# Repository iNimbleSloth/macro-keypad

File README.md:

# macro-keypad
A small USB macro keypad designed to use Cherry MX or pin compatible switches.

Here’s an accompanying video showing the macro keypad in more detail.

See the use, design and coding on [YouTube](https://www.youtube.com/watch?v=2TVdBebZfKo)

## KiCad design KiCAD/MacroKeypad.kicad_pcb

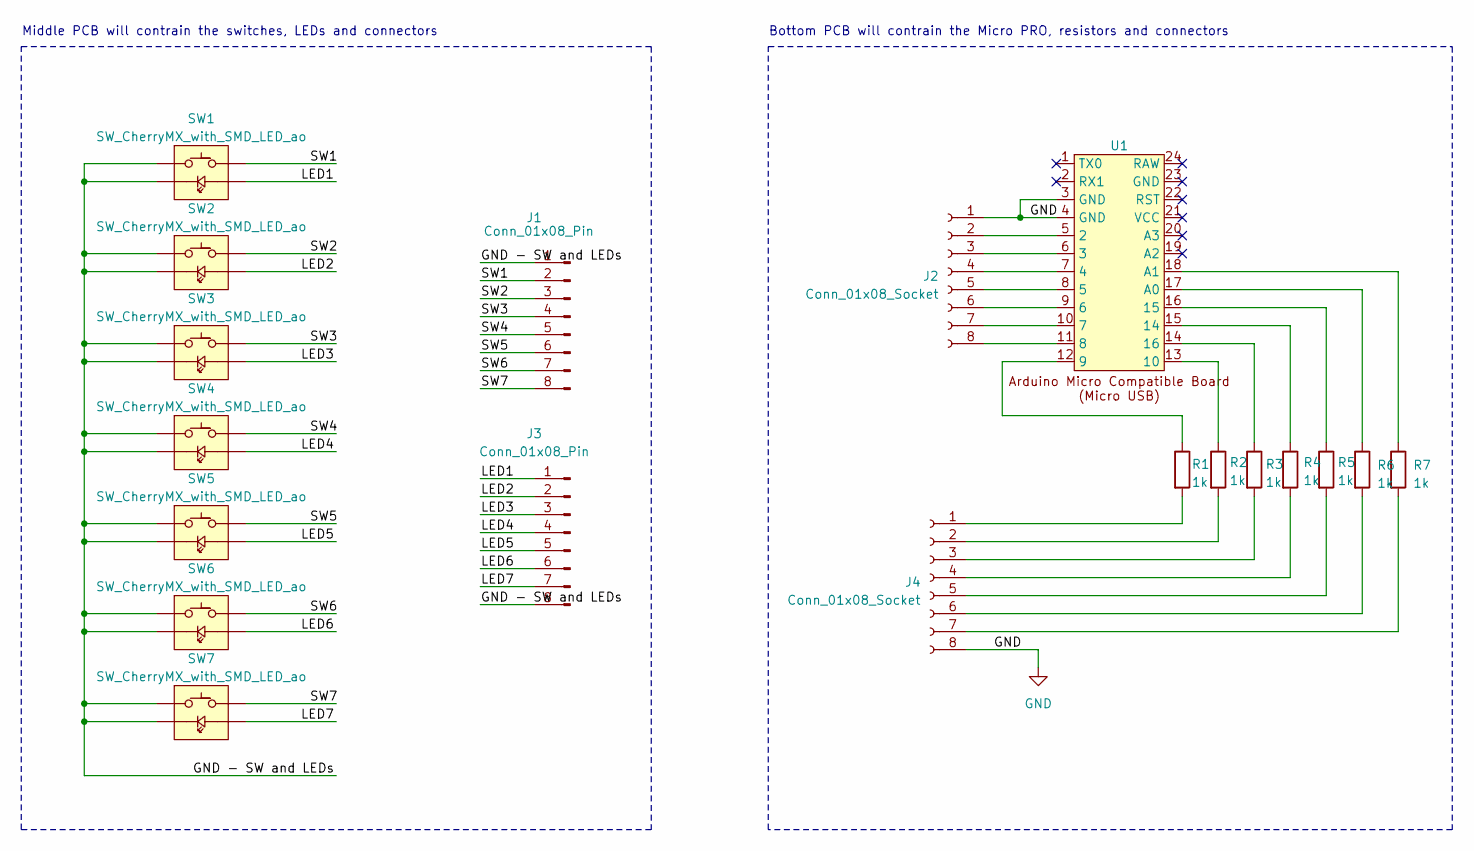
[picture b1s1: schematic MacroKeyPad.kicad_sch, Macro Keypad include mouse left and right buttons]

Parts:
J1, J3: Conn_01x08_Pin; PinHeader_1x08_P2.54mm_Vertical
J2, J4: Conn_01x08_Socket; PinSocket_1x08_P2.54mm_Vertical
R1, R2, R3, R4, R5, R6, R7: 1k; R_Axial_DIN0207_L6.3mm_D2.5mm_P10.16mm_Horizontal
SW1, SW2, SW3, SW4, SW5, SW6, SW7: SW_CherryMX_with_SMD_LED_ao; SW_Cherry_MX_1.00u_PCB_with SMD LED.kicad_AO
U1: ArduinoMicroCompatibleBoard

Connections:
/GND - SW and LEDs: J1.1, J3.8, SW1.1, SW1.3 (K), SW2.1, SW2.3 (K), SW3.1, SW3.3 (K), SW4.1, SW4.3 (K), SW5.1, SW5.3 (K), SW6.1, SW6.3 (K), SW7.1, SW7.3 (K)
/LED1: J3.1, SW1.4 (A)
/LED2: J3.2, SW2.4 (A)
/LED3: J3.3, SW3.4 (A)
/LED4: J3.4, SW4.4 (A)
/LED5: J3.5, SW5.4 (A)
/LED6: J3.6, SW6.4 (A)
/LED7: J3.7, SW7.4 (A)
/SW1: J1.2, SW1.2
/SW2: J1.3, SW2.2
/SW3: J1.4, SW3.2
/SW4: J1.5, SW4.2
/SW5: J1.6, SW5.2
/SW6: J1.7, SW6.2
/SW7: J1.8, SW7.2
GND: J2.1, J4.8, U1.3 (GND), U1.4 (GND)
unnamed: J2.2, U1.5 (2)
unnamed: J2.3, U1.6 (3)
unnamed: J2.4, U1.7 (4)
unnamed: J2.5, U1.8 (5)
unnamed: J2.6, U1.9 (6)
unnamed: J2.7, U1.10 (7)
unnamed: J2.8, U1.11 (8)
unnamed: J4.1, R1.2
unnamed: J4.2, R2.2
unnamed: J4.3, R3.2
unnamed: J4.4, R4.2
unnamed: J4.5, R5.2
unnamed: J4.6, R6.2
unnamed: J4.7, R7.2
unnamed: R1.1, U1.12 (9)
unnamed: R2.1, U1.13 (10)
unnamed: R4.1, U1.15 (14)
unnamed: R5.1, U1.16 (15)
unnamed: R3.1, U1.14 (16)
unnamed: R6.1, U1.17 (A0)
unnamed: R7.1, U1.18 (A1)

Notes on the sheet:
Bottom PCB will contrain the Micro PRO, resistors and connectors
Middle PCB will contrain the switches, LEDs and connectors

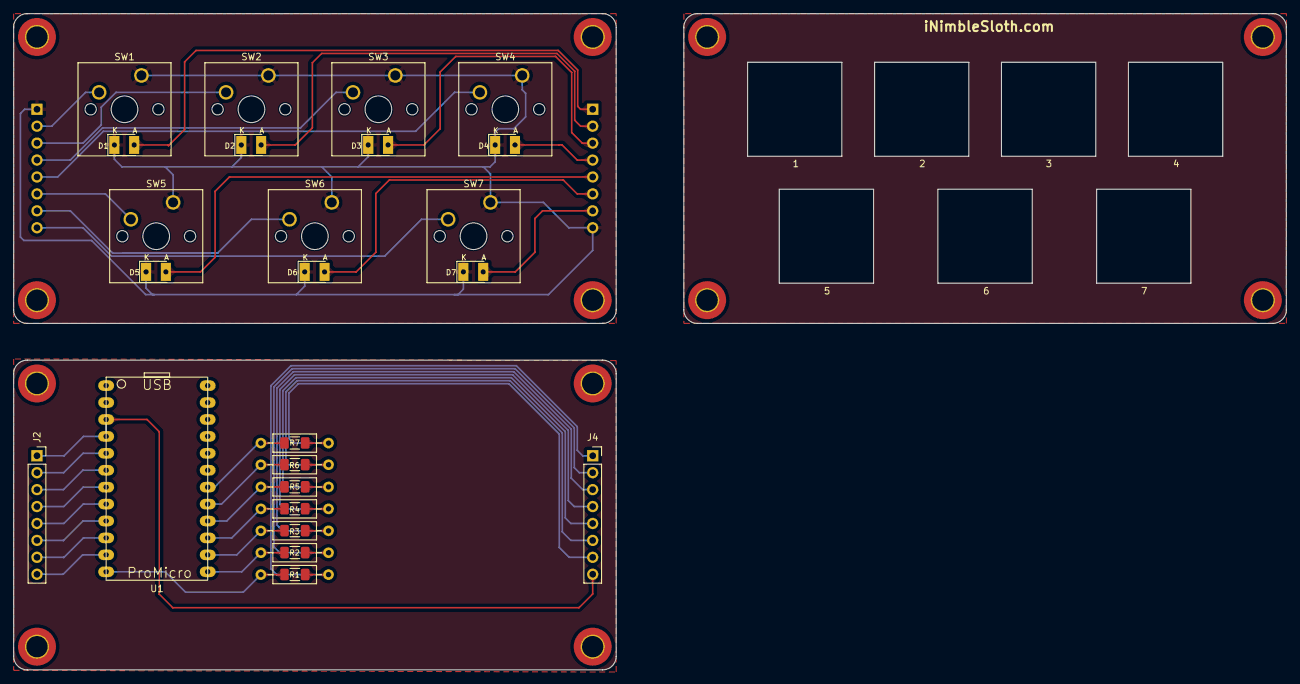
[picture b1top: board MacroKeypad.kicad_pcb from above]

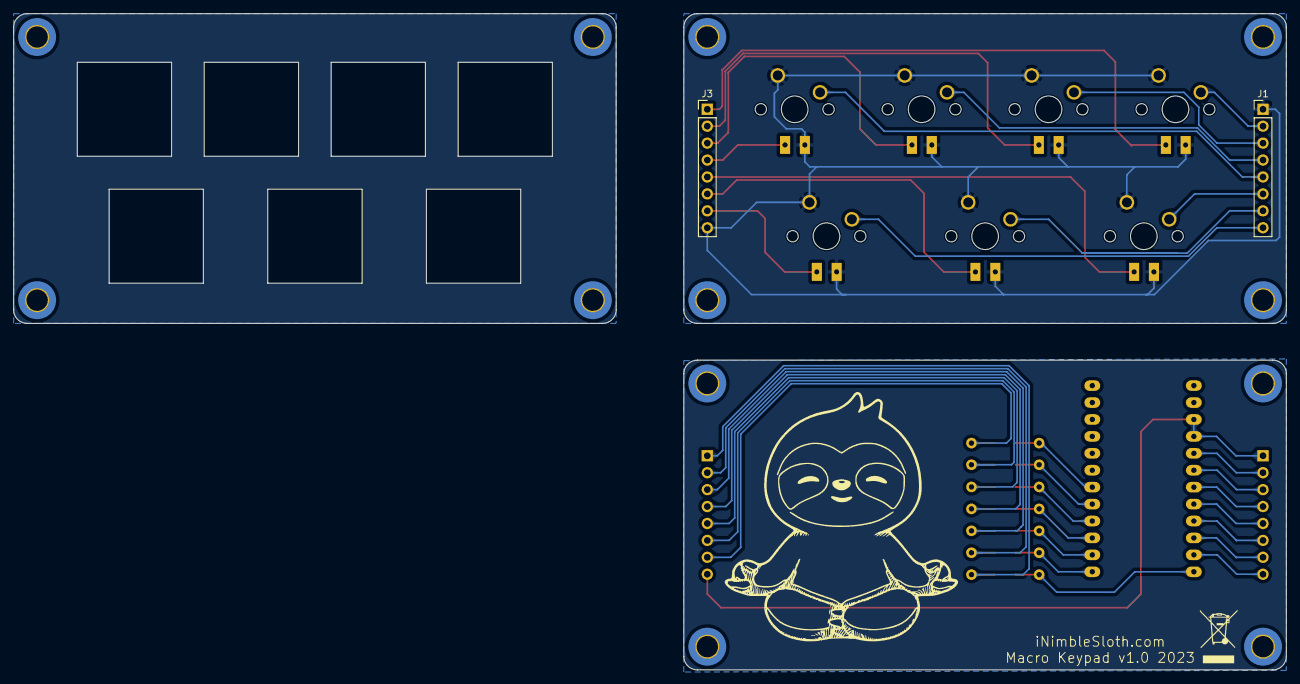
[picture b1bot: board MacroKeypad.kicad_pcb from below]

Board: 2 copper layers, 191.0 x 98.5 mm, 19 parts (2 on the bottom side), 37 nets.

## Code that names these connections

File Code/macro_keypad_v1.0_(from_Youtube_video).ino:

 /*  Macro Keypad
  by iNimbleSloth.com
  April 2023
*/
#include <Keyboard.h>
#include <Mouse.h>

//Create names for I/O; SW for input switches & led for LEDs in the switches.
//The Number is the Arduino pin out NOT the PCB pinout!!
int sw1 = 2;
int sw2 = 3;
int sw3 = 4;
int sw4 = 5;
int sw5 = 6;
int sw6 = 7;
int sw7 = 8;
int led1 = 9;
int led2 = 10;
int led3 = 16;
int led4 = 14;
int led5 = 15;
int led6 = 18;
int led7 = 19;

// variables to keep strack of button states
bool copyState = false;       // set initial state of Copy to false, i.e copy key not held down
bool pasteState = false;      // set initial state of paste to false, i.e copy key not held down
bool sw1State = false;        // set initial sate of sw1 to false
bool sw2State = false;        // set initial sate of sw2 to false
bool sw3State = false;        // set initial sate of sw3 to false
bool sw4State = false;        // set initial sate of sw4 to false
//bool sw5State = false;        // set initial sate of sw5 to false
//bool sw6State = false;        // set initial sate of sw6 to false
bool sw7State = false;        // set initial sate of sw7 to false

void setup() {

  Serial.begin(9600);           //serial output used for debugging (not required for release version)

  //setup I/O; SW inputs with internal pull up resistor. LEDs as outputs.
  pinMode(sw1, INPUT_PULLUP);
  pinMode(sw2, INPUT_PULLUP);
  pinMode(sw3, INPUT_PULLUP);
  pinMode(sw4, INPUT_PULLUP);
  pinMode(sw5, INPUT_PULLUP);
  pinMode(sw6, INPUT_PULLUP);
  pinMode(sw7, INPUT_PULLUP);
  pinMode(led1, OUTPUT);
  pinMode(led2, OUTPUT);
  pinMode(led3, OUTPUT);
  pinMode(led4, OUTPUT);
  pinMode(led5, OUTPUT);
  pinMode(led6, OUTPUT);
  pinMode(led7, OUTPUT);
}

//Main program loop starts here.
void loop() {
  //Serial.println("Start of Loop ");

  //SW1
  // IF SW1 is pressed AND the sw1State status is false (i.e. not already pressed), then type text
  if (digitalRead(sw1) == LOW && sw1State == false)
  {
    digitalWrite(led1, HIGH);
    sw1State = true;
    Keyboard.println("Case ");
    Keyboard.println("Create cLibrary acount and add username to contact in Salesforce.");
    Keyboard.println("Send through new technical contact lead.");
    delay(50);
  }
    
  // IF SW1 is released AND the sw3State status is true (i.e. button just released), then turn off the LED on the  button (SW1/LED1)
  if (digitalRead(sw1) == HIGH && sw1State == true)
  {
    digitalWrite(led1, LOW);
    sw1State = false;
    delay(50);
  }
    
  //SW2
  // IF SW2 is pressed AND the sw4State status is false (i.e. not already pressed), then type text
  if (digitalRead(sw2) == LOW && sw2State == false)
  {
    digitalWrite(led2, HIGH);
    sw2State = true;
    Keyboard.println("Created cLibrary acount and added username to contact in Salesforce.");
    Keyboard.println("Sent through new technical contact lead.");
    delay(50);
  }
    
  // IF SW4 is released AND the sw2State status is true (i.e. button just released), then turn off the LED on the snip button (SW2/LED2)
  if (digitalRead(sw2) == HIGH && sw2State == true)
  {
    digitalWrite(led2, LOW);
    sw2State = false;
    delay(50);
  }

  //SW3
  // IF SW3 is pressed and the sw5State status is false (i.e. not already pressed), then press type text
  if (digitalRead(sw3) == LOW && sw3State == false)
  {
    digitalWrite(led3, HIGH);
    sw3State = true;
    Keyboard.println("Case ");
    Keyboard.println("Create academy account.");
    Keyboard.println("Send lead through to quote for training.");
    delay(50);
  }
    
  // IF SW3 is released AND the snipeState status is true (i.e. button just released), then turn off the LED on the snip button (SW5/LED5)
  if (digitalRead(sw3) == HIGH && sw3State == true)
  {
    digitalWrite(led3, LOW);
    sw3State = false;
    delay(50);
  }

  //SW4 
  // IF SW4 is pressed and the sw4State status is false (i.e. not already pressed), then press type text
  if (digitalRead(sw4) == LOW && sw4State == false)
  {
    digitalWrite(led4, HIGH);
    sw4State = true;
    Keyboard.println("Created academy account.");
    Keyboard.println("Sent lead through to quote for training.");
    delay(50);
  }
    
  // IF SW4 is released AND the snipeState status is true (i.e. button just released), then turn off the LED on the snip button (SW4/LED4)
  if (digitalRead(sw4) == HIGH && sw4State == true)
  {
    digitalWrite(led4, LOW);
    sw4State = false;
    delay(50);
  }
    
  //SW5
  // IF SW5 is pressed and the copyState status is false (i.e. not already pressed), then execute Windows COPY command
  if (digitalRead(sw5) == LOW && copyState == false)
  {
    digitalWrite(led5, HIGH);
    copyState = true;
    Serial.println("Windows COPY command START");
    Keyboard.press(KEY_LEFT_CTRL);
    Keyboard.write('c');
    Keyboard.release(KEY_LEFT_CTRL);
    delay(50);
  }
    
  // IF SW5 is released AND the copyState status is true (i.e. button just released), then turn off the LED on the COPY button (SW5/LED5)
  if (digitalRead(sw5) == HIGH && copyState == true)
  {
    digitalWrite(led5, LOW);
    copyState = false;
    Serial.println("Windows COPY command END");
    delay(50);
  }

  //SW6 
  // IF SW6 is pressed AND the pasteState status is false (i.e. not already pressed), then execute Windows PASTE command
  if (digitalRead(sw6) == LOW && pasteState == false)
  {
    digitalWrite(led6, HIGH);
    pasteState = true;
    Serial.println("Windows PASTE command START");
    Keyboard.press(KEY_LEFT_CTRL);
    Keyboard.write('v');
    Keyboard.release(KEY_LEFT_CTRL);
    delay(50);
  }
    
  // IF SW6 is released AND the pasteState status is true (i.e. button just released), then turn off the LED on the PASTE button (SW3/LED3)
  if (digitalRead(sw6) == HIGH && pasteState == true)
  {
    digitalWrite(led6, LOW);
    pasteState = false;
    Serial.println("Windows PASTE command END");
    delay(50);
  }

  // IF SW7 is pressed and the sw7State status is false (i.e. not already pressed), then press execuste Windows DESKTOP command
  if (digitalRead(sw7) == LOW && sw7State == false)
  {
    digitalWrite(led7, HIGH);
    sw7State = true;
    Serial.println("Windows Desktop command START");
    Keyboard.press(KEY_LEFT_GUI);
    Keyboard.write('d');
    Keyboard.release(KEY_LEFT_GUI);
    delay(50);
  }

  // IF SW7 is NOT pressed and the rightClick status is true (i.e. the button has just been released), then release the right mouse button
  if(digitalRead(sw7) == HIGH && sw7State == true)
  {
    digitalWrite(led7, LOW);
    sw7State = false;
    delay(50);
  }

}

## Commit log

2023-05-01 Create KiCAD
2023-05-01 Create files
2023-05-01 Create file
2023-07-10 Rename macro_keypad.ino to macro_keypad_v1.0_(from_Youtube_video).ino
2023-07-10 Create macro_keypad_v1.1_(added_2nd_page).ino
    Version 1.1 uses button 7 (sw7) to toggle between two "pages" of buttons. LED 7 is used for feedback as to the currently selected page.
    LED 7 OFF = Page 1 (default upon power on)
    LED 7 ON = Page 2
2023-07-10 Create Codmacro_keypad_v1.1_(two pages).ino
    Button 7 (SW7) toggles between two "pages" of buttons.
    LED 7 gives feedback as to page;
    - LED7 OFF = Page 1 (default upon power on)
    - LED ON = Page 2
2023-07-10 Rename Codmacro_keypad_v1.1_(two pages).ino to Code/macro_keypad_v1.1_(two pages).ino
2024-08-08 Add files via upload
    Added switch symbol and footprint as per request on YouTube.
